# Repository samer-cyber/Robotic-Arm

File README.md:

# Six-Axis Robot Arm

A six-axis arm built from scratch around 3D-printed cycloidal gearboxes. This
repo has everything: the gearbox generator for Fusion 360, print files,
ESP32 firmware, a browser control panel with a 3D digital twin and 6-DOF IK,
the wiring schematic, and the September vision experiments.

|  |  |
|---|---|
| Overhead camera + 3-DOF IK reaching for a box (Sept 2026) | Testing an inverted cycloidal gearbox |

More video and the story behind it: [samerhaddadin.me/work/robotic-arm](https://samerhaddadin.me/work/robotic-arm).

## The arm

| | |
|---|---|
| Axes | J1 base yaw, J2 shoulder, J3 elbow, J4 wrist pitch, J5 wrist roll, J6 wrist pitch, plus a tendon hand |
| J1-J3 | NEMA 17 (17HS4401S) + TMC2209 over UART, through printed **inverted cycloidal** boxes: **16:1, 21:1, 16:1** |
| J4-J6 | MG996R / MG995, 270° hobby servos |
| Hand | one continuous-rotation MG995 winding the tendons |
| Links | J2→J3 130 mm, J3→J4 130 mm |
| Controller | ESP32-WROOM-32, USB serial to a PC |
| Camera | Luxonis OAK-D SR, overhead (used by the vision pipeline) |

The gearbox housings are part of the links. Each joint's motor and pin carrier
sit in one link, and its roller drum is printed into the next. Because the
drum is the part that turns, the ratio is the **roller count**, and the drum
turns the same way as the motor. See [docs/gearbox.md](docs/gearbox.md).

## Status

- **Works:** all six joints move. Firmware 1.3.0 drives them, and the panel and
  twin control them. IK reaches arbitrary poses in the twin.
- **Fixed in this release, not yet checked on the arm:** gear ratios (the
  firmware used 15/20/15), the gripper's open/close logic, and the 21-roller
  disc B, which interferes with its ring in the CAD.
  [docs/calibration.md](docs/calibration.md) is the 20-minute checklist.
- **Next:** teleoperation from a Quest 3, then learning from demonstrations.
  See the [roadmap](docs/roadmap.md).

## Quick start

```bash
# firmware (PlatformIO)
cd firmware && pio run -t upload

# panel + twin, with or without the arm plugged in
pip install pyserial numpy
python host/control.py              # or: --simulate
# open the printed URL, then "3D twin"
```

The gearbox generator: [hardware/gearbox-generator](hardware/gearbox-generator).
The wiring: [docs/wiring.md](docs/wiring.md).

## Repository map

| Folder | |
|---|---|
| [`firmware/`](firmware) | `arm-fw`: ESP32 joint controller, PlatformIO |
| [`host/`](host) | `armlink` Python driver, kinematics, simulator, control panel, 3D twin |
| [`description/`](description) | `arm.json`, link meshes from the CAD, generated URDF |
| [`hardware/gearbox-generator/`](hardware/gearbox-generator) | Fusion 360 cycloidal joint generator v7 (+ the v6 scripts) |
| [`hardware/stl/`](hardware/stl) | print files: arm links (`Body 1-7`) and gearbox parts |
| [`hardware/electronics/wiring/`](hardware/electronics/wiring) | as-built wiring schematic (KiCad 9, PDF) |
| [`hardware/electronics/can-stepper-node/`](hardware/electronics/can-stepper-node) | unfinished per-joint CAN driver board (ESP32-C3, TMC2209, MT6701) |
| [`hardware/calculators/`](hardware/calculators) | sizing spreadsheets |
| [`ros2/`](ros2) | September 3-DOF vision pipeline, ROS 2 Jazzy on WSL (legacy) |
| [`docs/`](docs) | calibration, wiring, gearbox notes, roadmap |
| [`archive/`](archive) | the first 3-DOF test rig firmware and superseded prints |

`Body N` in `hardware/stl/arm` is the Fusion body name: 1 base, 2 turret
(J1 drum + J2 motor), 3 upper arm (J2 + J3 drums), 4 forearm (J3 motor + J4
servo), 5-7 wrist.

## License

- Software (`firmware/`, `host/`, `ros2/`, `description/tools/`, generator
  scripts): [MIT](LICENSE)
- Hardware (CAD, STL, KiCad, `description/` meshes):
  [CERN-OHL-P-2.0](LICENSE-HARDWARE)

The hand on the end is a third-party design and is not part of this repo.

Built by [Samer Haddadin](https://samerhaddadin.me).

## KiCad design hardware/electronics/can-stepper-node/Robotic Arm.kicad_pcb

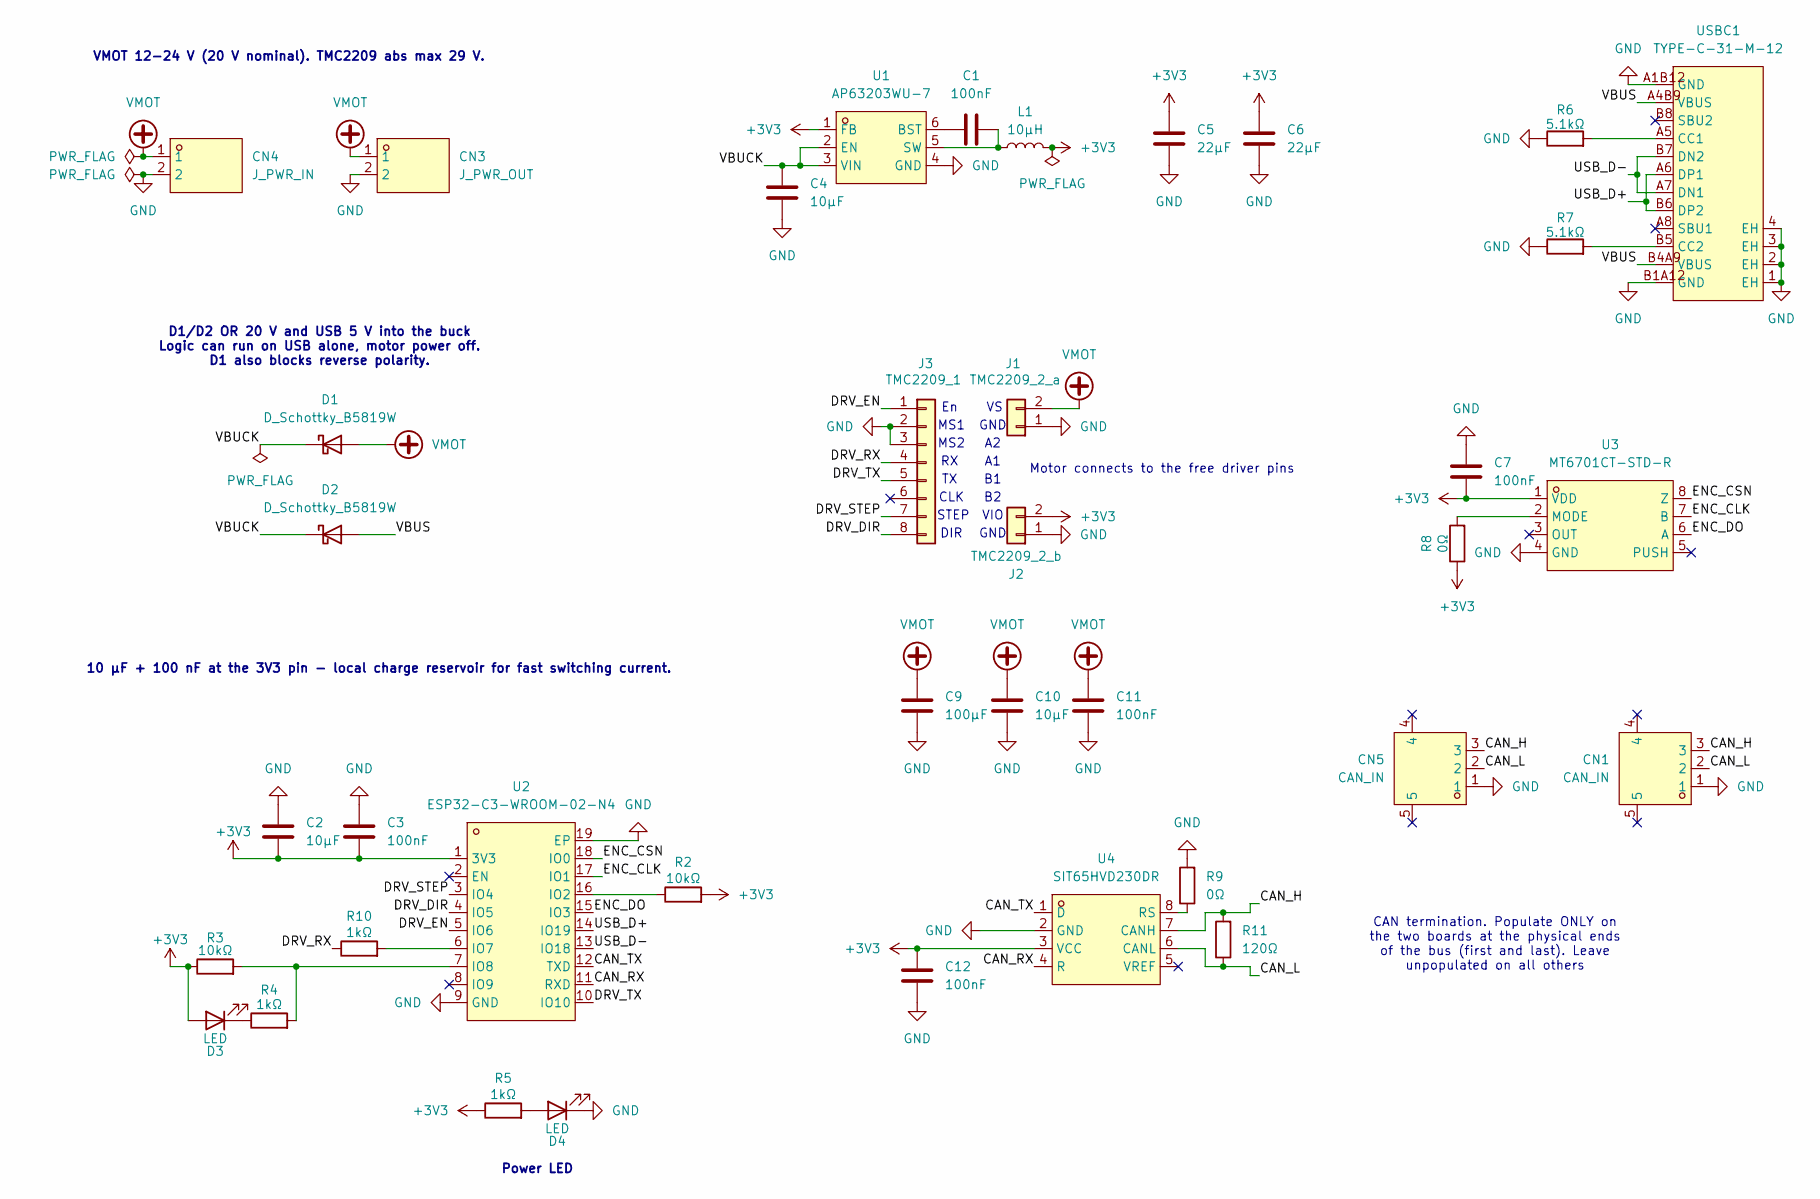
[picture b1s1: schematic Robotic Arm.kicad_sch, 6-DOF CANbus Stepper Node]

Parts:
C1, C3, C7, C11, C12: 100nF; C_0603_1608Metric
C2, C4, C10: 10µF; C_1206_3216Metric
C5, C6: 22µF; C_0805_2012Metric
C9: 100µF; CP_Radial_D8.0mm_P3.50mm
CN1, CN5: CAN_IN; CONN-SMD_SM03B-SRSS-TB-LF-SN-P; MPN SM03B-SRSS-TB(LF)(SN); LCSC Part C160403
CN3: J_PWR_OUT; CONN-TH_S2P-VH-LF-SN; MPN S2P-VH(LF)(SN); LCSC Part C160355
CN4: J_PWR_IN; CONN-TH_S2P-VH-LF-SN; MPN S2P-VH(LF)(SN); LCSC Part C160355
D1, D2: D_Schottky_B5819W; D_SOD-123
D3, D4: LED; LED_0603_1608Metric
J1: TMC2209_2_a; PinSocket_1x02_P2.54mm_Vertical
J2: TMC2209_2_b; PinSocket_1x02_P2.54mm_Vertical
J3: TMC2209_1; PinSocket_1x08_P2.54mm_Vertical
L1: 10µH; L_Changjiang_FNR4020S
R2, R3: 10kΩ; R_0603_1608Metric
R4, R5, R10: 1kΩ; R_0603_1608Metric
R6, R7: 5.1kΩ; R_0603_1608Metric
R8, R9: 0Ω; R_0603_1608Metric
R11: 120Ω; R_0603_1608Metric
U1: AP63203WU-7; TSOT-26_L2.9-W1.6-P0.95-LS2.8-BL; MPN AP63203WU-7; LCSC Part C780769
U2: ESP32-C3-WROOM-02-N4; BULETM-SMD_ESPRESSIF_ESP32-C3-WROOM-02-N4-4MB; MPN ESP32-C3-WROOM-02-N4; LCSC Part C2934560
U3: MT6701CT-STD-R; SOP-8_L4.9-W3.9-P1.27-LS6.0-BL; MPN MT6701CT-STD-R; LCSC Part C3003196
U4: SIT65HVD230DR; SOP-8_L4.9-W3.9-P1.27-LS6.0-BL; MPN SIT65HVD230DR; LCSC Part C496619
USBC1: TYPE-C-31-M-12; USB-C_SMD-TYPE-C-31-M-12_1; MPN TYPE-C-31-M-12; LCSC Part C165948

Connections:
+3V3: C2.2, C3.2, C5.1, C6.1, C7.2, C12.1, D3.2 (A), J2.2, L1.2, R2.2, R3.1, R5.1, R8.1, U1.1 (FB), U2.1 (3V3), U3.1 (VDD), U4.3 (VCC); also elsewhere on the board
/CAN_H: CN1.3, CN5.3, R11.2, U4.7 (CANH)
/CAN_L: CN1.2, CN5.2, R11.1, U4.6 (CANL)
/CAN_RX: U2.11 (RXD), U4.4 (R)
/CAN_TX: U2.12 (TXD), U4.1 (D)
/DRV_DIR: J3.8, U2.4 (IO5)
/DRV_EN: J3.1, U2.5 (IO6)
/DRV_RX: J3.4, R10.1
/DRV_STEP: J3.7, U2.3 (IO4)
/DRV_TX: J3.5, U2.10 (IO10)
/ENC_CLK: U2.17 (IO1), U3.7 (B)
/ENC_CSN: U2.18 (IO0), U3.8 (Z)
/ENC_DO: U2.15 (IO3), U3.6 (A)
/USB_D+: U2.14 (IO19), USBC1.A6 (DP1), USBC1.B6 (DP2)
/USB_D−: U2.13 (IO18), USBC1.A7 (DN1), USBC1.B7 (DN2)
/VBUCK: C4.1, D1.1 (K), D2.1 (K), U1.2 (EN), U1.3 (VIN)
/VBUS: D2.2 (A), USBC1.A4B9 (VBUS), USBC1.B4A9 (VBUS)
GND: C2.1, C3.1, C4.2, C5.2, C6.2, C7.1, C9.2, C10.2, C11.2, C12.2, CN1.1, CN3.2, CN4.2, CN5.1, D4.1 (K), J1.1, J2.1, J3.2, J3.3, R6.1, R7.1, R9.2, U1.4 (GND), U2.9 (GND), U2.19 (EP), U3.4 (GND), U4.2 (GND), USBC1.1 (EH), USBC1.2 (EH), USBC1.3 (EH), USBC1.4 (EH), USBC1.A1B12 (GND), USBC1.B1A12 (GND); also elsewhere on the board
unnamed: D3.1 (K), R4.1
unnamed: D4.2 (A), R5.2
unnamed: C1.1, U1.6 (BST)
unnamed: C1.2, L1.1, U1.5 (SW)
unnamed: R2.1, U2.16 (IO2)
unnamed: R10.2, U2.6 (IO7)
unnamed: R3.2, R4.2, U2.7 (IO8)
unnamed: R8.2, U3.2 (MODE)
unnamed: R9.1, U4.8 (RS)
unnamed: R6.2, USBC1.A5 (CC1)
unnamed: R7.2, USBC1.B5 (CC2)
VMOT: C9.1, C10.1, C11.1, CN3.1, CN4.1, D1.2 (A), J1.2

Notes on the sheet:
Power LED
Motor connects to the free driver pins
VIO
10 µF + 100 nF at the 3V3 pin - local charge reservoir for fast switching current.
CLK
VMOT 12-24 V (20 V nominal). TMC2209 abs max 29 V.
CAN termination. Populate ONLY on the two boards at the physical ends of the bus (first and last). Leave unpopulated on all others
STEP
MS1
D1/D2 OR 20 V and USB 5 V into the buck Logic can run on USB alone, motor power off. D1 also blocks reverse polarity.
MS2
GND
GND
DIR

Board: 2 copper layers, 40 parts (3 on the bottom side), 31 nets, no tracks yet.

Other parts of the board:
C8: 100nF; C_0603_1608Metric
R1: 10kΩ; R_0603_1608Metric

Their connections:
+3V3: R1.1; also elsewhere on the board
GND: C8.2; also elsewhere on the board
unnamed: C8.1, R1.2
